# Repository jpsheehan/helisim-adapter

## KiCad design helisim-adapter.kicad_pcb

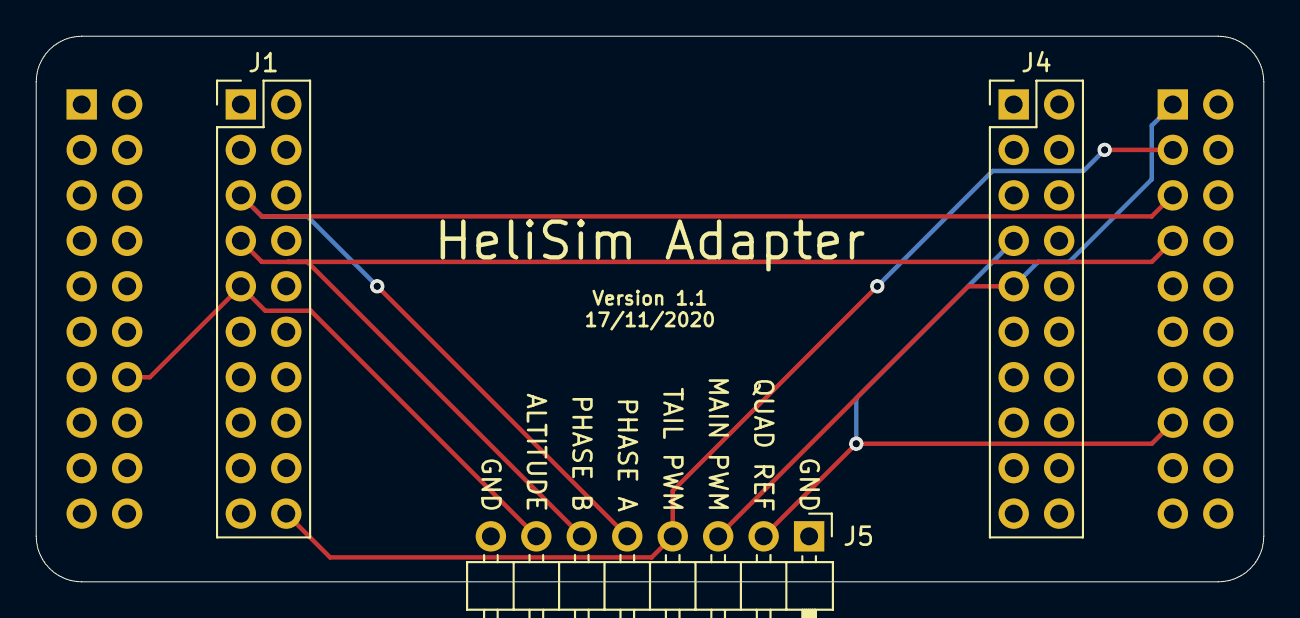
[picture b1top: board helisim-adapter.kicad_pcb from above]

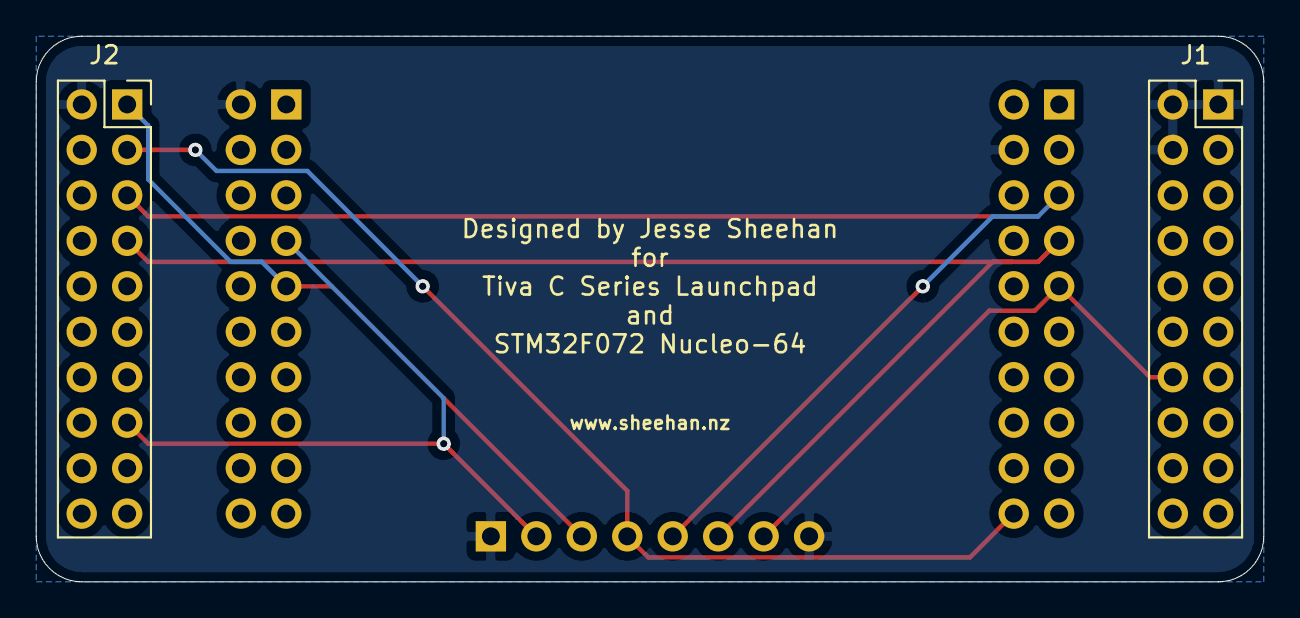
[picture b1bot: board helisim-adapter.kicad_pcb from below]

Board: 2 copper layers, 68.6 x 30.5 mm, 5 parts (2 on the bottom side), 7 nets.

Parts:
J1: TIVA_J1_J3; PinHeader_2x10_P2.54mm_Vertical
J1#2: NUCLEO_CN7; PinSocket_2x10_P2.54mm_Vertical
J2: NUCLEO_CN10; PinSocket_2x10_P2.54mm_Vertical
J4: TIVA_J4_J2; PinHeader_2x10_P2.54mm_Vertical
J5: HeliConn; PinHeader_1x08_P2.54mm_Horizontal

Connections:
/HELI_ALTITUDE: J1.9, J1#2.14, J5.7
/HELI_MAIN_PWM: J2.1, J4.9, J5.3
/HELI_PHASE_A: J1.5, J2.5, J5.5
/HELI_PHASE_B: J1.7, J2.7, J5.6
/HELI_QUAD_REF: J2.15, J4.7, J5.2
/HELI_TAIL_PWM: J1.20, J2.3, J5.4
GND: J1.4, J1#2.1, J1#2.2, J1#2.4, J2.2, J4.2, J5.1, J5.8

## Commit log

2020-08-25 First commit.
2020-11-16 Fixed silkscreen designator for tiva jumper
